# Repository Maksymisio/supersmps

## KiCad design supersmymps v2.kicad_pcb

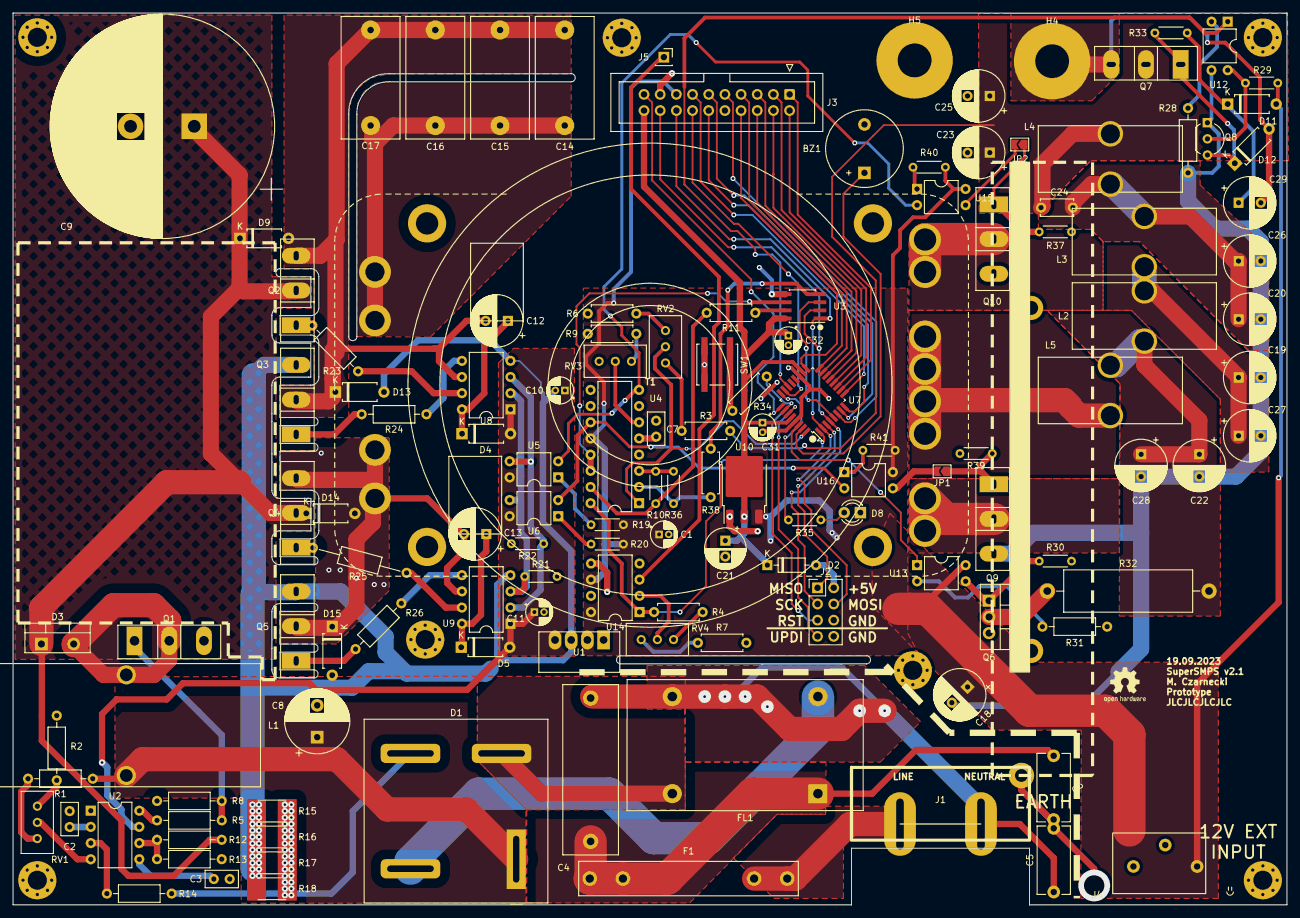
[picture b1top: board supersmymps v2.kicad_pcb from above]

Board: 2 copper layers, 200.0 x 140.0 mm, 131 parts (0 on the bottom side), 108 nets.

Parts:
BZ1: Buzzer; Buzzer_12x9.5RM7.6
C1, C31, C32: 1u/50V; CP_Radial_D4.0mm_P1.50mm
C2, C3: 10n; C_Disc_D5.0mm_W2.5mm_P2.50mm
C4: 0.47u; C_Rect_L26.5mm_W8.5mm_P22.50mm_MKS4
C5, C6: 4.7n; C_Disc_D10.5mm_W5.0mm_P10.00mm
C7: 1n; C_Disc_D5.0mm_W2.5mm_P2.50mm
C8: 6.8u/400V; CP_Radial_D10.0mm_P5.00mm
C9: 470u/400V; CP_Radial_D35.0mm_P10.00mm_SnapIn
C10, C11: 1u; CP_Radial_D4.0mm_P1.50mm
C12, C13: 470u; CP_Radial_D8.0mm_P3.50mm
C14, C15, C16, C17: 0.33u; C_Rect_L19.0mm_W9.0mm_P15.00mm_MKS4
C18, C29: 470u/16V; CP_Radial_D8.0mm_P3.50mm
C19, C20, C22, C23, C25, C26, C27, C28: 100u/63V; CP_Radial_D8.0mm_P3.50mm
C21: 220u/6.3V; CP_Radial_D6.3mm_P2.50mm
C24: 1u/10V; C_Disc_D5.0mm_W2.5mm_P5.00mm
D1: kbpc1510; Diode_Bridge_GeneSiC_KBPC_T
D2: BAT48RL; D_DO-35_SOD27_P7.62mm_Horizontal
D3: FES16JT; TO-220-2_Vertical
D4, D5, D9, D11, D13, D14, D15: IN4002; D_A-405_P7.62mm_Horizontal
D8: RUN; LED_D3.0mm
D12: 12V; D_A-405_P7.62mm_Horizontal
F1: Fuse; Fuseholder_Littelfuse_445_030_series_5x30mm
FL1: Filter_EMI_CommonMode; L_CommonMode_Toroid_Vertical_L36.8mm_W20.3mm_Px15.24mm_Py22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
H4: +; MountingHole_5.3mm_M5_Pad
H5: -; MountingHole_5.3mm_M5_Pad
J1: C14 socket; C14 AC socket
J2: programmer; PinHeader_2x04_P2.54mm_Vertical
J3: Front_Panel; IDC-Header_2x10_P2.54mm_Vertical
J4: Conn_01x03_Socket; aosi connector 3 pin 45 degrees
J5: Wire (it's copper); PinSocket_1x01_P2.54mm_Vertical
JP1, JP2: SolderJumper_2_Open; SolderJumper-2_P1.3mm_Open_TrianglePad1.0x1.5mm
L1: 5u; L_Toroid_Vertical_L41.9mm_W19.1mm_P15.80mm_Vishay_TJ7
L2, L3, L5: 3.2u; L_Toroid_Vertical_L22.4mm_W10.2mm_P7.90mm_Vishay_TJ4
L4: 3.958u; L_Toroid_Vertical_L22.4mm_W10.2mm_P7.90mm_Vishay_TJ4
Q1, Q2, Q3, Q4, Q5: IRFP360; TO-247-3_Vertical
Q6: IRFZ44N; TO-220-3_Vertical
Q7: IRFP3006; TO-247-3_Vertical
Q8: MPSA42; TO-92_Inline_Wide
Q9, Q10: IRFP4321; TO-247-3_Vertical
R1: 330k; R_Axial_DIN0207_L6.3mm_D2.5mm_P10.16mm_Horizontal
R2: 4.7k; R_Axial_DIN0207_L6.3mm_D2.5mm_P10.16mm_Horizontal
R3: 330k; R_Axial_DIN0207_L6.3mm_D2.5mm_P7.62mm_Horizontal
R4: 560k; R_Axial_DIN0207_L6.3mm_D2.5mm_P7.62mm_Horizontal
R5, R23, R24, R26: 3.3; R_Axial_DIN0207_L6.3mm_D2.5mm_P10.16mm_Horizontal
R6: 36k; R_Axial_DIN0207_L6.3mm_D2.5mm_P7.62mm_Horizontal
R7: 6.8k; R_Axial_DIN0207_L6.3mm_D2.5mm_P7.62mm_Horizontal
R8: 100k; R_Axial_DIN0207_L6.3mm_D2.5mm_P10.16mm_Horizontal
R9: 5.1k; R_Axial_DIN0207_L6.3mm_D2.5mm_P7.62mm_Horizontal
R10, R29, R30, R36: 10k; R_Axial_DIN0204_L3.6mm_D1.6mm_P5.08mm_Horizontal
R11, R38: 22; R_Axial_DIN0207_L6.3mm_D2.5mm_P7.62mm_Horizontal
R12: 910k; R_Axial_DIN0207_L6.3mm_D2.5mm_P10.16mm_Horizontal
R13: 15k; R_Axial_DIN0207_L6.3mm_D2.5mm_P10.16mm_Horizontal
R14: 220; R_Axial_DIN0207_L6.3mm_D2.5mm_P10.16mm_Horizontal
R15, R16, R17, R18: 300m; R_2512_6332Metric_Pad1.40x3.35mm_HandSolder
R19, R20, R40, R41: 470; R_Axial_DIN0204_L3.6mm_D1.6mm_P5.08mm_Horizontal
R21, R22, R33, R35, R37, R39: 1k; R_Axial_DIN0204_L3.6mm_D1.6mm_P5.08mm_Horizontal
R25: 3.3; R_Axial_DIN0207_L6.3mm_D2.5mm_P15.24mm_Horizontal
R28, R31: 330; R_Axial_DIN0207_L6.3mm_D2.5mm_P10.16mm_Horizontal
R32: 1/5W; R_Axial_Power_L20.0mm_W6.4mm_P25.40mm
R34: 330; R_Axial_DIN0207_L6.3mm_D2.5mm_P7.62mm_Horizontal
RV1, RV2, RV3, RV4: 10k; Potentiometer_Bourns_3296W_Vertical
SW1: SW_Push; SW_Push_1P1T_NO_CK_KSC6xxJ
T1: Transformer_1P_2S; BIG toroid max custom
U1: BS1212S; SIP-4
U2: ICE1PCS02; DIP-8_W7.62mm
U3: TLV5638; PowerIntegrations_SO-8
U4: TL494; DIP-16_W7.62mm
U5, U6, U12, U13, U15, U16: TLP421P; DIP-4_W7.62mm
U7: AVR64DA32x-xPT; TQFP-32_7x7mm_P0.8mm
U8, U9: FAN7382; DIP-8_W7.62mm
U10: LM1117DT-5.0; TO-252-3_TabPin2
U14: NE5532; DIP-8_W7.62mm

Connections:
300V clean: C9.1, D3.1 (K), D9.1 (K), D14.1 (K), Q2.2 (D), Q4.2 (D), R12.1
+5V: C21.1, C31.1, C32.1, D2.1 (K), J3.20, U3.8 (VDD), U7.18 (AVDD), U7.28 (VDD), U10.2 (VO)
+12V: C1.1, C18.1, D11.2 (A), J3.15, J4.3, R19.1, R20.1, R29.1, R40.1, R41.1, U1.2 (12VIN), U4.12 (VCC), U10.3 (VI), U13.4, U14.6 (-), U14.8 (V+), U15.4, U16.4
+12VA: C10.1, C11.1, D4.2 (A), D5.2 (A), U1.4 (12VOUT), U2.7 (VCC), U5.4, U6.4, U8.1 (VCC), U9.1 (VCC)
/7SEG_A: J3.5, U7.14 (PD4)
/7SEG_B: J3.6, U7.15 (PD5)
/7SEG_C: J3.7, U7.16 (PD6)
/7SEG_D: J3.8, U7.17 (VREFA/PD7)
/7SEG_DEMUX_A: J3.1, U7.10 (PD0)
/7SEG_DEMUX_B: J3.2, U7.11 (PD1)
/7SEG_DEMUX_C: J3.3, U7.12 (PD2)
/7SEG_DEMUX_D: J3.4, U7.13 (PD3)
/+HALF_RECT: Q10.2 (D), T1.3 (SA)
/-HALF_RECT: Q9.2 (D), T1.6 (SD)
/DRIVE_1: R21.1, U6.3, U8.2 (HIN), U9.3 (LIN)
/DRIVE_2: R22.1, U5.3, U8.3 (LIN), U9.2 (HIN)
/FILTER1: C22.1, C28.1, L2.1, L5.2, R32.2
/FILTER2: C19.1, C27.1, L2.2, L3.1
/FILTER3: C20.1, C24.1, C26.1, L3.2, L4.1
/LIVE_FUSED: C4.1, C6.1, F1.2, FL1.1
/PFC_SHUNT: D1.3 (-), R14.1, R15.1, R16.1, R17.1, R18.1
/S+: U4.11 (C2), U6.2, U16.2
/S-: U4.8 (C1), U5.2, U15.2
/live filtered: D1.2, FL1.2
/neut filtered: D1.4, FL1.4
/rectified 300V: C8.1, D1.1 (+), L1.1, R1.1
ADC_CUR: R4.2, U4.16 (2IN+), U7.1 (PA3), U14.1
ADC_VOL: RV2.2, U4.1 (1IN+), U7.32 (PA2)
BUZZER: BZ1.1 (-), U7.31 (PA1)
CROWBAR: U7.30 (PA0), U13.1
DAC_CUR: R11.1, U3.7 (OUTB)
DAC_REF: U3.6 (REF), U4.13 (OUTCTRL), U4.14 (REF)
DAC_VOL: R38.1, U3.4 (OUTA)
DAC_~CS: U3.3 (~CS), U7.5 (PA7)
DISPLAY_~CS: J3.19, U7.25 (PF5)
Earth: C5.2, C6.2, J1.3 (EARTH)
FAN_PWM: J3.14, U7.23 (PF3)
GND: C2.2, C3.2, C8.2, C9.2, C10.2, C11.2, D13.2 (A), D15.2 (A), Q1.3 (S), Q3.3 (S), Q5.3 (S), R2.2, R8.1, R13.1, R15.2, R16.2, R17.2, R18.2, R21.2, R22.2, U1.3 (GNDOUT), U2.1 (GND), U8.4 (COM), U9.4 (COM)
GND1: BZ1.2 (+), C1.2, C7.2, C18.2, C19.2, C20.2, C21.2, C22.2, C23.2, C25.2, C26.2, C27.2, C28.2, C31.2, C32.2, D8.1 (K), H5.1, J2.6, J2.8, J3.10, J3.17, J4.2, Q6.3 (S), Q8.1 (E), Q9.3 (S), Q10.3 (S), R6.1, R7.1, R9.2, R28.2, R30.2, R31.2, R37.2, R39.2, SW1.1, U1.1 (GNDIN), U3.5 (AGND), U4.4 (DTC), U4.7 (GND), U4.9 (E1), U4.10 (E2), U7.19 (GND), U7.29 (GND), U10.1 (GND), U12.3, U14.4 (V-), U14.5 (+)
IBUS: J5.1, U14.3 (+)
LV_RECT: L5.1, T1.4 (SB), T1.5 (SC)
NEUT: C4.2, C5.1, FL1.3, J1.2 (AC_N)
unnamed: D2.2 (A), J2.2
unnamed: D3.2 (A), L1.2, Q1.2 (D)
unnamed: C12.1, D4.1 (K), U8.8 (VB)
unnamed: C13.1, D5.1 (K), U9.8 (VB)
unnamed: D8.2 (A), R35.2
unnamed: C29.1, D11.1 (K), R33.1
unnamed: D12.1 (K), Q7.1 (G), Q8.3 (C), R33.2
unnamed: C12.2, C14.1, C15.1, C16.1, C17.1, D9.2 (A), D13.1 (K), Q2.3 (S), Q3.2 (D), U8.6 (VS)
unnamed: C13.2, D14.2 (A), D15.1 (K), Q4.3 (S), Q5.2 (D), T1.2 (AB), U9.6 (VS)
unnamed: JP1.1 (A), Q9.1 (G), R39.1
unnamed: JP1.2 (B), U16.3
unnamed: JP2.1 (A), Q10.1 (G), R37.1
unnamed: JP2.2 (B), U15.3
unnamed: Q2.1 (G), R23.2
unnamed: Q3.1 (G), R24.2
unnamed: Q4.1 (G), R25.2
unnamed: Q5.1 (G), R26.2
unnamed: Q6.2 (D), R32.1
unnamed: Q6.1 (G), R30.1, U13.3
unnamed: Q8.2 (B), R29.2, U12.4
unnamed: R1.2, RV1.1
unnamed: R2.1, RV1.3
unnamed: R3.1, RV2.1
unnamed: R4.1, RV4.3
unnamed: R6.2, RV2.3
unnamed: R7.2, RV4.1
unnamed: R9.1, RV3.3
unnamed: R19.2, U5.1
unnamed: R20.2, U6.1
unnamed: R28.1, U12.2
unnamed: R31.1, U13.2
unnamed: R34.2, SW1.2
unnamed: R40.2, U15.1
unnamed: R41.2, U16.1
unnamed: C14.2, C15.2, C16.2, C17.2, T1.1 (AA)
unnamed: R5.1, U2.8 (GATE)
unnamed: C2.1, U2.2 (ICOMP)
unnamed: C3.1, U2.5 (VCOMP)
unnamed: RV1.2, U2.4 (VINS)
unnamed: R12.2, R13.2, U2.6 (VSENSE)
unnamed: R36.2, R38.2, U4.2 (1IN-)
unnamed: R10.1, R11.2, U4.15 (2IN-)
unnamed: C7.1, U4.5 (CT)
unnamed: R10.2, R36.1, U4.3 (FB)
unnamed: RV3.2, U4.6 (RT)
unnamed: R35.1, U7.24 (PF4)
unnamed: R23.1, U8.7 (HO)
unnamed: R24.1, U8.5 (LO)
unnamed: R25.1, U9.7 (HO)
unnamed: R26.1, U9.5 (LO)
unnamed: RV4.2, U14.2 (-)
OUTPUT_CONTROL: U7.22 (PF2), U12.1
PFC1: Q1.1 (G), R5.2, R8.2
PFC_ISENSE: R14.2, U2.3 (ISENSE)
SPI_CLK: J2.3, J3.18, U3.2 (SCLK), U7.4 (PA6)
SPI_MISO: J2.1, U7.3 (PA5)
SPI_MOSI: J2.4, J3.16, U3.1 (DIN), U7.2 (PA4)
UI_0: J3.9, U7.6 (PC0)
UI_1: J3.11, U7.7 (PC1)
UI_2: J3.12, U7.8 (PC2)
UI_3: J3.13, U7.9 (PC3)
UPDI: J2.7, U7.27 (UPDI)
VAC: F1.1, J1.1 (AC_P)
VBUS: C23.1, C24.2, C25.1, L4.2, Q7.2 (D), R3.2
VDC: C29.2, D12.2 (A), H4.1, Q7.3 (S)
~RESET: J2.5, R34.1, U7.26 (~RESET/PF6)

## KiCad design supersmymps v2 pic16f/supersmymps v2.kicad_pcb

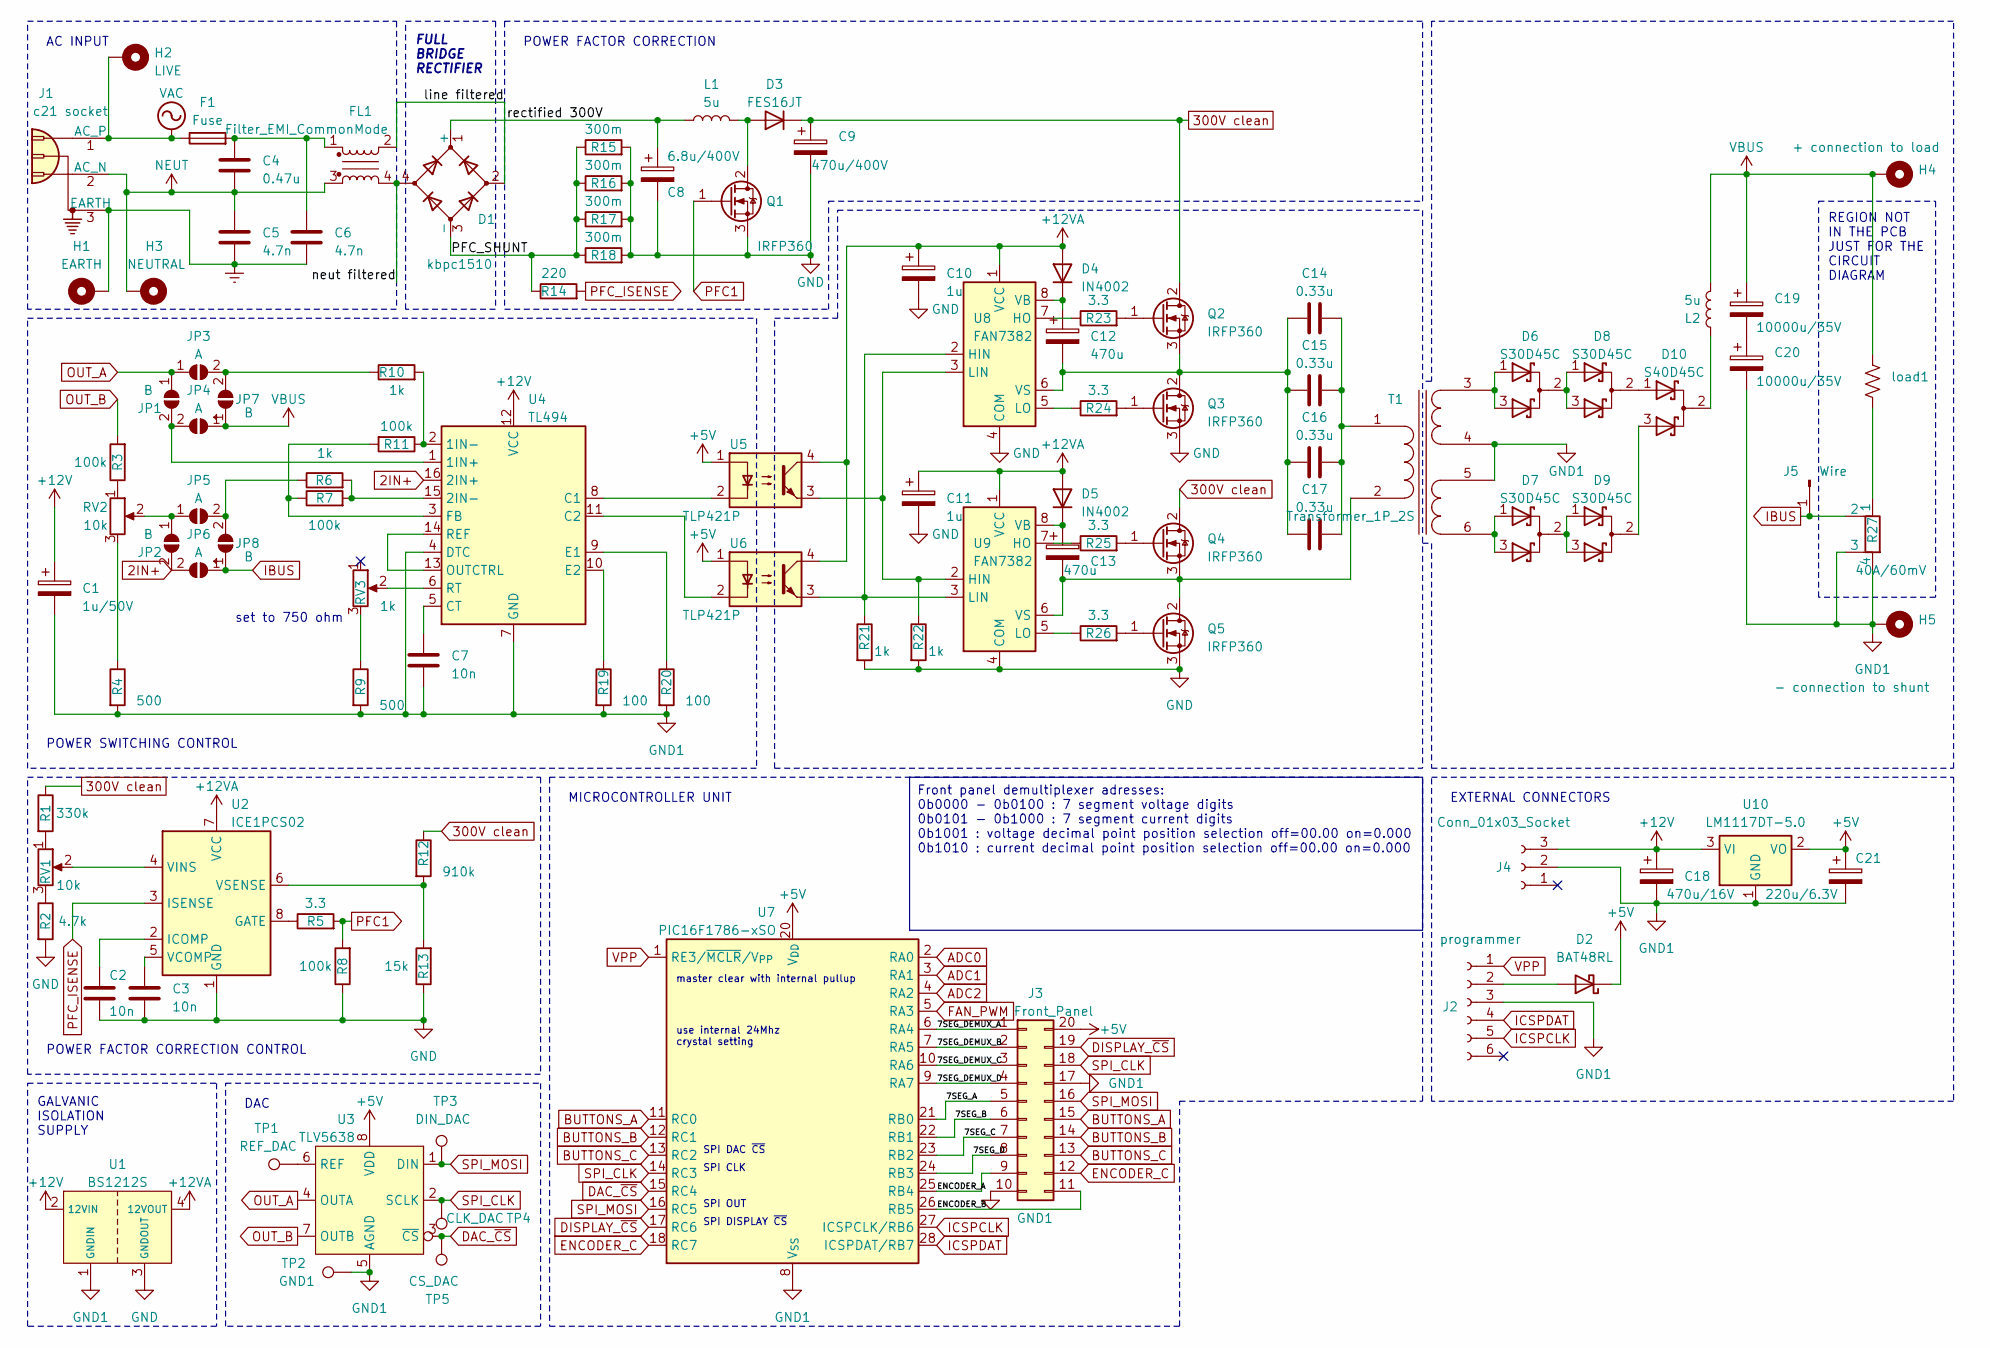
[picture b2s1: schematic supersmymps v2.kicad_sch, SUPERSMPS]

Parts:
C1: 1u/50V; CP_Radial_D4.0mm_P1.50mm
C2, C3, C7: 10n; C_Disc_D5.0mm_W2.5mm_P2.50mm
C4: 0.47u; C_Rect_L26.5mm_W8.5mm_P22.50mm_MKS4
C5, C6: 4.7n; C_Disc_D10.5mm_W5.0mm_P10.00mm
C8: 6.8u/400V; CP_Radial_D10.0mm_P5.00mm
C9: 470u/400V; CP_Radial_D35.0mm_P10.00mm_SnapIn
C10, C11: 1u; CP_Radial_D4.0mm_P1.50mm
C12, C13: 470u; CP_Radial_D8.0mm_P3.50mm
C14, C15, C16, C17: 0.33u; C_Rect_L19.0mm_W9.0mm_P15.00mm_MKS4
C18: 470u/16V; CP_Radial_D8.0mm_P3.50mm
C19, C20: 10000u/35V; CP_Radial_D30.0mm_P10.00mm_SnapIn
C21: 220u/6.3V; CP_Radial_D6.3mm_P2.50mm
D1: kbpc1510; Diode_Bridge_GeneSiC_KBPC_T
D2: BAT48RL; D_DO-35_SOD27_P7.62mm_Horizontal
D3: FES16JT; TO-220-2_Vertical
D4, D5: IN4002; D_A-405_P7.62mm_Horizontal
D6, D7, D8, D9: S30D45C; TO-247-3_Vertical
D10: S40D45C; TO-247-3_Vertical
F1: Fuse; Fuseholder_Littelfuse_445_030_series_5x30mm
FL1: Filter_EMI_CommonMode; L_CommonMode_Toroid_Vertical_L36.8mm_W20.3mm_Px15.24mm_Py22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
H1: EARTH; MountingHole_6mm_Pad
H2: LIVE; MountingHole_6mm_Pad
H3: NEUTRAL; MountingHole_6mm_Pad
H4: + connection to load; MountingHole_5.3mm_M5_Pad
H5: - connection to shunt; MountingHole_5.3mm_M5_Pad
J1: c21 socket
J2: programmer; PinHeader_1x06_P2.54mm_Vertical
J3: Front_Panel; PinHeader_2x10_P2.54mm_Vertical
J4: Conn_01x03_Socket; aosi connector 3 pin 45 degrees
J5: Wire; PinSocket_1x01_P2.54mm_Vertical
JP1, JP2, JP7, JP8: B; SolderJumper-2_P1.3mm_Open_RoundedPad1.0x1.5mm
JP3, JP4, JP5, JP6: A; SolderJumper-2_P1.3mm_Open_RoundedPad1.0x1.5mm
L1, L2: 5u; L_Toroid_Vertical_L41.9mm_W19.1mm_P15.80mm_Vishay_TJ7
Q1, Q2, Q3, Q4, Q5: IRFP360; TO-247-3_Vertical
R1: 330k; R_Axial_DIN0207_L6.3mm_D2.5mm_P10.16mm_Horizontal
R2: 4.7k; R_Axial_DIN0207_L6.3mm_D2.5mm_P10.16mm_Horizontal
R3, R7, R8, R11: 100k; R_Axial_DIN0207_L6.3mm_D2.5mm_P10.16mm_Horizontal
R4, R9: 500; R_Axial_DIN0207_L6.3mm_D2.5mm_P10.16mm_Horizontal
R5, R23, R24, R25, R26: 3.3; R_Axial_DIN0207_L6.3mm_D2.5mm_P10.16mm_Horizontal
R6, R10, R21, R22: 1k; R_Axial_DIN0204_L3.6mm_D1.6mm_P5.08mm_Horizontal
R12: 910k; R_Axial_DIN0207_L6.3mm_D2.5mm_P10.16mm_Horizontal
R13: 15k; R_Axial_DIN0207_L6.3mm_D2.5mm_P10.16mm_Horizontal
R14: 220; R_Axial_DIN0207_L6.3mm_D2.5mm_P10.16mm_Horizontal
R15, R16, R17, R18: 300m; R_2512_6332Metric_Pad1.40x3.35mm_HandSolder
R19, R20: 100; R_Axial_DIN0207_L6.3mm_D2.5mm_P10.16mm_Horizontal
R27: 40A/60mV
RV1, RV2: 10k; Potentiometer_Bourns_3296W_Vertical
RV3: 1k; Potentiometer_Bourns_3296W_Vertical
T1: Transformer_1P_2S; BIG toroid max custom
TP1: REF_DAC; TestPoint_Pad_D2.0mm
TP2: GND1; TestPoint_Pad_D2.0mm
TP3: DIN_DAC; TestPoint_Pad_D2.0mm
TP4: CLK_DAC; TestPoint_Pad_D2.0mm
TP5: CS_DAC; TestPoint_Pad_D2.0mm
U1: BS1212S; SIP-4
U2: ICE1PCS02; DIP-8_W7.62mm
U3: TLV5638; PowerIntegrations_SO-8
U4: TL494; DIP-16_W7.62mm
U5, U6: TLP421P; DIP-4_W7.62mm
U7: PIC16F1786-xSO; SOIC-28W_7.5x17.9mm_P1.27mm
U8, U9: FAN7382; DIP-8_W7.62mm
U10: LM1117DT-5.0; TO-252-3_TabPin2
load1: (no value)

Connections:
2IN+: JP2.2 (B), JP6.2 (B), U4.16 (2IN+)
300V clean: C9.1, D3.1 (K), Q2.2 (D), Q4.2 (D), R1.1, R12.1
+5V: C21.1, D2.1 (K), J3.20, U3.8 (VDD), U5.1, U6.1, U7.20 (V_{DD}), U10.2 (VO)
+12V: C1.1, C18.1, J4.3, U1.2 (12VIN), U4.12 (VCC), U10.3 (VI)
+12VA: C10.1, C11.1, D4.2 (A), D5.2 (A), U1.4 (12VOUT), U2.7 (VCC), U5.4, U6.4, U8.1 (VCC), U9.1 (VCC)
/7SEG_A: J3.5, U7.21 (RB0)
/7SEG_B: J3.6, U7.22 (RB1)
/7SEG_C: J3.7, U7.23 (RB2)
/7SEG_D: J3.8, U7.24 (RB3)
/7SEG_DEMUX_A: J3.1, U7.6 (RA4)
/7SEG_DEMUX_B: J3.2, U7.7 (RA5)
/7SEG_DEMUX_C: J3.3, U7.10 (RA6)
/7SEG_DEMUX_D: J3.4, U7.9 (RA7)
/ENCODER_A: J3.9, U7.25 (RB4)
/ENCODER_B: J3.11, U7.26 (RB5)
/PFC_SHUNT: D1.3 (-), R14.1, R15.1, R16.1, R17.1, R18.1
/line filtered: D1.2, FL1.2
/neut filtered: D1.4, FL1.4
/rectified 300V: C8.1, D1.1 (+), L1.1
ADC0: U7.2 (RA0)
ADC1: U7.3 (RA1)
ADC2: U7.4 (RA2)
ADC3: U7.5 (RA3)
BUTTONS_A: J3.15, U7.11 (RC0)
BUTTONS_B: J3.14, U7.12 (RC1)
BUTTONS_C: J3.13, U7.13 (RC2)
DAC_~CS: TP5.1, U3.3 (~CS), U7.15 (RC4)
DISPLAY_~CS: J3.19, U7.17 (RC6)
ENCODER_C: J3.12, U7.18 (RC7)
Earth: C5.2, C6.2, H1.1, J1.3 (EARTH)
GND: C2.2, C3.2, C8.2, C9.2, C10.2, C11.2, Q1.3 (S), Q3.3 (S), Q5.3 (S), R2.2, R8.1, R13.1, R15.2, R16.2, R17.2, R18.2, R21.2, R22.2, U1.3 (GNDOUT), U2.1 (GND), U8.4 (COM), U9.4 (COM)
GND1: C1.2, C7.2, C18.2, C20.2, C21.2, H5.1, J2.3, J3.10, J3.17, J4.2, R4.2, R9.2, R19.2, R20.2, R27.3, R27.4, T1.4 (SB), T1.5 (SC), TP2.1, U1.1 (GNDIN), U3.5 (AGND), U4.4 (DTC), U4.7 (GND), U7.8 (V_{SS}), U7.19 (V_{SS}), U10.1 (GND); also elsewhere on the board
IBUS: J5.1, JP6.1 (A), JP8.1 (A), R27.2
ICSPCLK: J2.5, U7.27 (ICSPCLK/RB6)
ICSPDAT: J2.4, U7.28 (ICSPDAT/RB7)
NEUT: C4.2, C5.1, FL1.3, H3.1, J1.2 (AC_N)
unnamed: C4.1, C6.1, F1.2, FL1.1
unnamed: C19.2, C20.1
unnamed: D2.2 (A), J2.2
unnamed: D3.2 (A), L1.2, Q1.2 (D)
unnamed: C12.1, D4.1 (K), U8.8 (VB)
unnamed: C13.1, D5.1 (K), U9.8 (VB)
unnamed: D6.2 (A), D8.1 (K), D8.3 (K)
unnamed: D7.2 (A), D9.1 (K), D9.3 (K)
unnamed: D8.2 (A), D10.1 (K)
unnamed: D9.2 (A), D10.3 (K)
unnamed: D10.2 (A), L2.1
unnamed: JP1.2 (B), JP4.2 (B), U4.1 (1IN+)
unnamed: JP2.1 (A), JP5.1 (A), RV2.2
unnamed: JP3.2 (B), JP7.2 (B), R10.1
unnamed: JP5.2 (B), JP8.2 (B), R6.1
unnamed: Q2.1 (G), R23.2
unnamed: C12.2, C14.1, C15.1, C16.1, C17.1, Q2.3 (S), Q3.2 (D), U8.6 (VS)
unnamed: Q3.1 (G), R24.2
unnamed: Q4.1 (G), R25.2
unnamed: C13.2, Q4.3 (S), Q5.2 (D), T1.2 (AB), U9.6 (VS)
unnamed: Q5.1 (G), R26.2
unnamed: R1.2, RV1.1
unnamed: R2.1, RV1.3
unnamed: R3.1, RV2.1
unnamed: R4.1, RV2.3
unnamed: R9.1, RV3.3
unnamed: R27.1, load1.2
unnamed: C14.2, C15.2, C16.2, C17.2, T1.1 (AA)
unnamed: D6.1 (K), D6.3 (K), T1.3 (SA)
unnamed: D7.1 (K), D7.3 (K), T1.6 (SD)
unnamed: R5.1, U2.8 (GATE)
unnamed: C2.1, U2.2 (ICOMP)
unnamed: C3.1, U2.5 (VCOMP)
unnamed: RV1.2, U2.4 (VINS)
unnamed: R12.2, R13.2, U2.6 (VSENSE)
unnamed: TP1.1, U3.6 (REF)
unnamed: R10.2, R11.1, U4.2 (1IN-)
unnamed: R6.2, R7.2, U4.15 (2IN-)
unnamed: U4.8 (C1), U5.2
unnamed: U4.11 (C2), U6.2
unnamed: C7.1, U4.5 (CT)
unnamed: R20.1, U4.9 (E1)
unnamed: R19.1, U4.10 (E2)
unnamed: R7.1, R11.2, U4.3 (FB)
unnamed: U4.13 (OUTCTRL), U4.14 (REF)
unnamed: RV3.2, U4.6 (RT)
unnamed: R21.1, U6.3, U8.2 (HIN), U9.3 (LIN)
unnamed: R23.1, U8.7 (HO)
unnamed: R22.1, U5.3, U8.3 (LIN), U9.2 (HIN)
unnamed: R24.1, U8.5 (LO)
unnamed: R25.1, U9.7 (HO)
unnamed: R26.1, U9.5 (LO)
OUT_A: JP1.1 (A), JP3.1 (A), U3.4 (OUTA)
OUT_B: R3.2, U3.7 (OUTB)
PFC1: Q1.1 (G), R5.2, R8.2
PFC_ISENSE: R14.2, U2.3 (ISENSE)
SPI_CLK: J3.18, TP4.1, U3.2 (SCLK), U7.14 (RC3)
SPI_MOSI: J3.16, TP3.1, U3.1 (DIN), U7.16 (RC5)
VAC: F1.1, H2.1, J1.1 (AC_P)
VBUS: C19.1, H4.1, JP4.1 (A), JP7.1 (A), L2.2, load1.1
VPP: J2.1, U7.1 (RE3/~MCLR/V_{PP})

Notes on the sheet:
Front panel demultiplexer adresses: 0b0000 - 0b0100 : 7 segment voltage digits 0b0101 - 0b1000 : 7 segment current digits 0b1001 : voltage decimal point position selection off=00.00 on=0.000 0b1010 : current decimal point position selection off=00.00 on=0.000
DAC
MICROCONTROLLER UNIT
REGION NOT IN THE PCB JUST FOR THE CIRCUIT DIAGRAM
POWER FACTOR CORRECTION CONTROL
AC INPUT
set to 750 ohm
master clear with internal pullup
SPI CLK
POWER FACTOR CORRECTION
SPI OUT
EXTERNAL CONNECTORS
SPI DAC ~{CS}
FULL BRIDGE RECTIFIER
POWER SWITCHING CONTROL
SPI DISPLAY ~{CS}
use internal 24Mhz crystal setting
GALVANIC ISOLATION SUPPLY

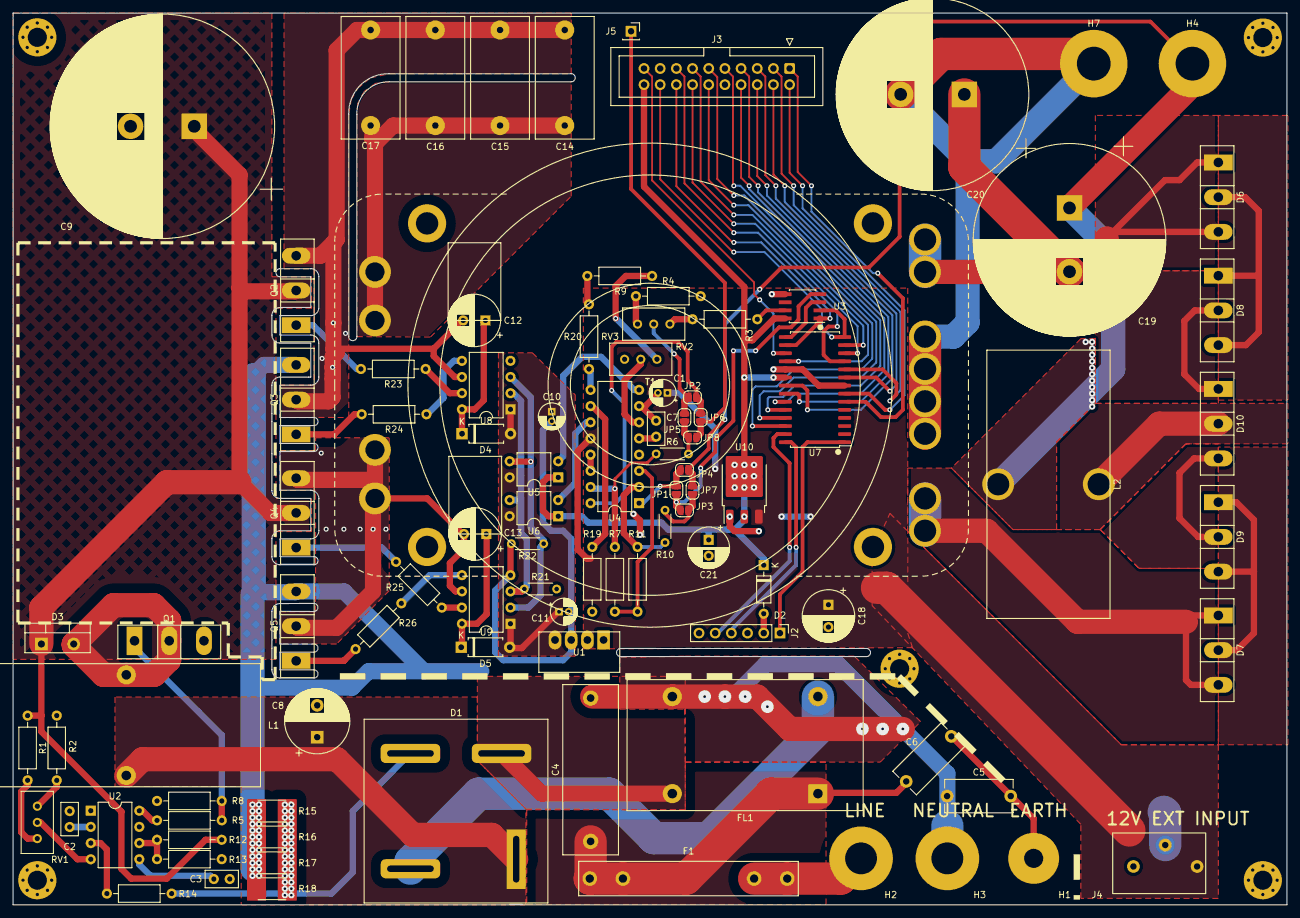
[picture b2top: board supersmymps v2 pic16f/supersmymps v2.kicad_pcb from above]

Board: 2 copper layers, 200.0 x 140.0 mm, 97 parts (0 on the bottom side), 91 nets.

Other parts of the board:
H7: output -; MountingHole_5.3mm_M5_Pad

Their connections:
GND1: H7.1; also elsewhere on the board

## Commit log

2023-11-23 Add files via upload
    Lets take a moment to brake the ice, so my intentions are known
2023-11-23 Add files via upload
    Close to finish
2023-12-27 One of the last versions before prototype is done.
    I have finally gotten rid of the solder jumpers because i'm now sure how the tl494 circuit works
